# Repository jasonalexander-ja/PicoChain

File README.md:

# PicoChain

Pico(Daisy)Chain is a simple standard for creating daisy chains of connected devices, allowing I2C and power to be easily distributed out using ethernet patch cables. 

This is a repository containing documentation and reference hardware + software implementations. 

All hardware reference implementations are in KiCAD 8+ format with the PCB layout and Gerbers. 

### Contents: 

- [PicoChainReference](/PicoChainReference); A generic reference design breaking out the power and I2C to pin headers, this can be easily adapted to what ever purpose is desired. 
- [PicoChainZero](/PicoChainZero); A reference design using the Raspberry Pi Zero as a I2C controller, breaks out the Pi Zero's serial to a USB-C connector. 
- [PicoChainTerminator](/PicoChainTerminator); A reference design for a termination endpoint device, one of these needs to be present at the start and end of a chain. 

## Design Overview 

PicoChain uses differential I2C, 12 + 24 volts, all sent down a single RJ45 & twisted pair allowing communication and power for microcontrollers + motors to be supplied using commonly available ethernet patch cables. 

Generation of the differential I2C is handled by the [NXP PCA9615](https://www.nxp.com/docs/en/data-sheet/PCA9615.pdf) meaning that when SCL and SCA is hooked up to this chip, all the same I2C libraries and implementation automatically work with no further modifications. 

The 12 + 24 volts is supplied with the assumption that this will be regulated into the relevant required voltages by the connected devices, the reference implementations regulates a 5V for the microcontroller and a 5V for servo and similar small motors off of the 12V line, and a 12V line is regulated off of the 24V line intended for high power motors. 

Each PicoChain device has 2 RJ45 connectors to send and receive power and data, they don't have a particular direction are all the reference designs have the RJ45s passively connected, tapping off of power and I2C as needed, however, all PicoChain chains need terminators at either end. 

Generally, this is designed for running sequences across some connected devices, with the idea that only 1 large load (I.E. a motor) will be running at a time, reducing the current load going through the patch cables and chained devices. 

### Pinout 

| **RJ45 Pin** | **Function** |
|--------------|--------------|
| **1**        | GND          |
| **2**        | +24V         |
| **3**        | DSDAM        |
| **4**        | DSCLM        |
| **5**        | DSCLP        |
| **6**        | DSDAP        |
| **7**        | GND          |
| **8**        | +12V         |

Pins 3-6 (inclusive) are generated by the [PCA9615](https://www.nxp.com/docs/en/data-sheet/PCA9615.pdf) and are connected directly to ICs on each device.

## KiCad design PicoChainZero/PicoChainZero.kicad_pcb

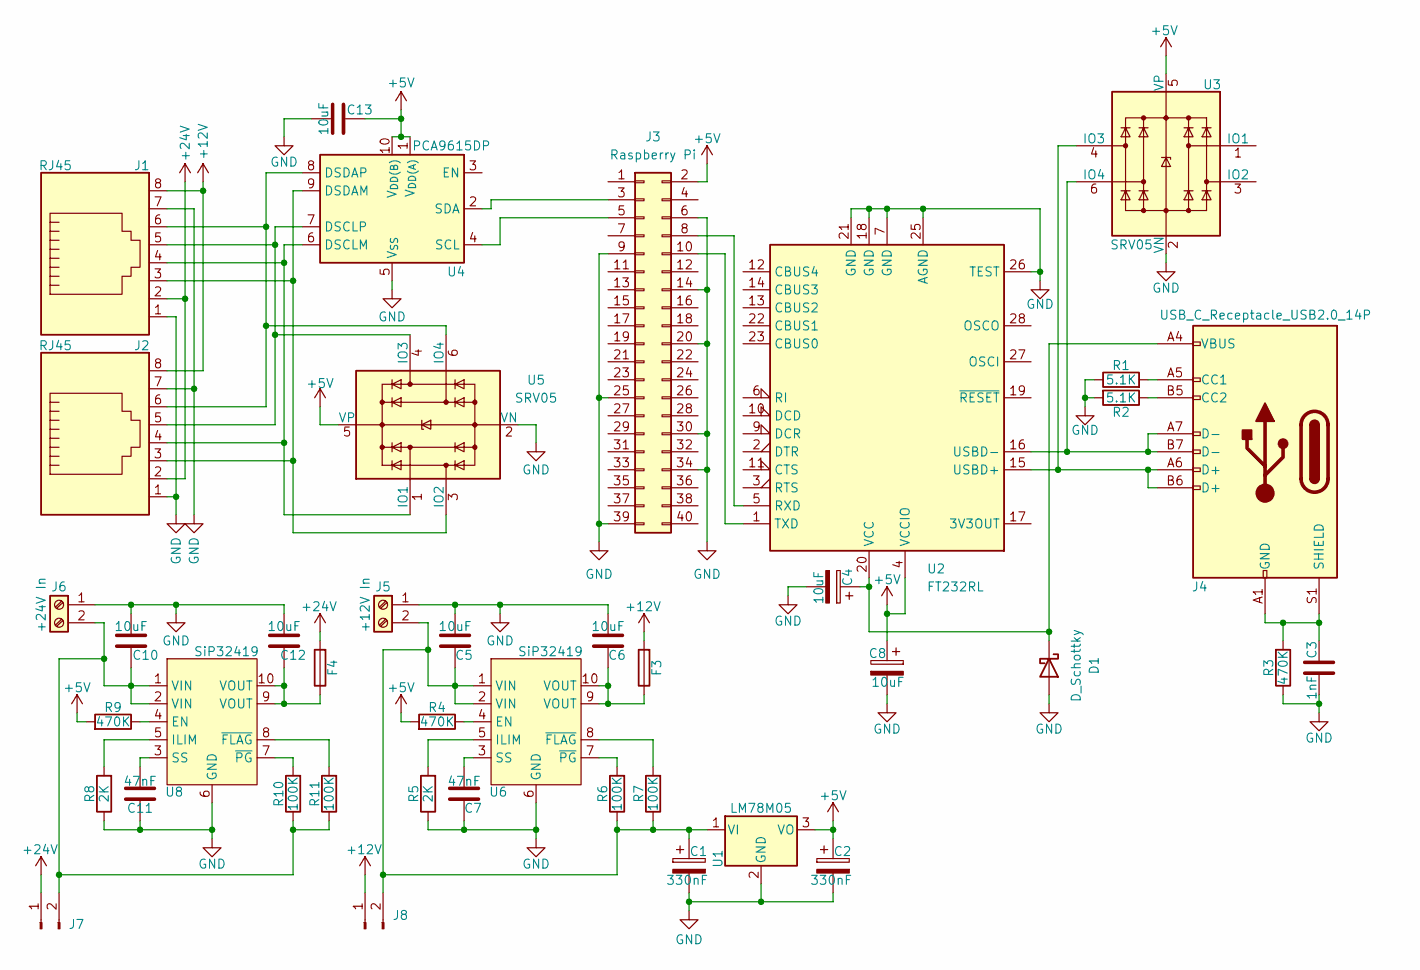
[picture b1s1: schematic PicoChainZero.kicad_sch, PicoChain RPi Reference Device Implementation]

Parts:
C1, C2: 330nF; CP_EIA-3216-18_Kemet-A
C3: 1nF; C_1206_3216Metric
C4, C8: 10uF; CP_EIA-3216-18_Kemet-A
C5, C6, C10, C12, C13: 10uF; C_0805_2012Metric
C7, C11: 47nF; C_0805_2012Metric
D1: D_Schottky; D_SMA
F3, F4: Fuse; Fuse_0805_2012Metric
J1, J2: RJ45; RJ45_Amphenol_54602-x08_Horizontal
J3: Raspberry Pi; PinHeader_2x20_P2.54mm_Vertical
J4: USB_C_Receptacle_USB2.0_14P; USB_C_Receptacle_GCT_USB4085
J5: +12V In; TerminalBlock_Phoenix_MKDS-1,5-2-5.08_1x02_P5.08mm_Horizont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
J6: +24V In; TerminalBlock_Phoenix_MKDS-1,5-2-5.08_1x02_P5.08mm_Horizont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
J7, J8: Conn_01x02_Pin; PinHeader_1x02_P2.54mm_Vertical
R1, R2: 5.1K; R_0805_2012Metric
R3, R4, R9: 470K; R_0805_2012Metric
R5, R8: 2K; R_0805_2012Metric
R6, R7, R10, R11: 100K; R_0805_2012Metric
U1: LM78M05; TO-252-2
U2: FT232RL; SSOP-28_5.3x10.2mm_P0.65mm
U3, U5: SRV05; SOT-23-6
U4: PCA9615DP; TSSOP-10_3x3mm_P0.5mm
U6, U8: SiP32419; DFN-10-1EP_3x3mm_P0.5mm_EP1.65x2.38mm

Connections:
+5V: C2.1, C8.1, C13.2, J3.2, R4.2, R9.2, U1.3 (VO), U2.4 (VCCIO), U3.5 (VP), U4.1 (V_{DD(A)}), U4.10 (V_{DD(B)}), U5.5 (VP)
+12V: F3.2, J1.8, J2.8, J8.1
+24V: F4.2, J1.2, J2.2, J7.1
GND: C1.2, C2.2, C3.2, C4.2, C5.1, C6.1, C7.2, C8.2, C10.1, C11.2, C12.1, C13.1, D1.2 (A), J1.1, J1.7, J2.1, J2.7, J3.6, J3.9, J3.14, J3.20, J3.25, J3.30, J3.34, J3.39, J5.1, J6.1, R1.1, R2.2, R3.1, R5.1, R8.1, U1.2 (GND), U2.7 (GND), U2.18 (GND), U2.21 (GND), U2.25 (AGND), U2.26 (TEST), U3.2 (VN), U4.5 (V_{SS}), U5.2 (VN), U6.6 (GND), U8.6 (GND)
unnamed: C6.2, F3.1, U6.9 (VOUT), U6.10 (VOUT)
unnamed: C12.2, F4.1, U8.9 (VOUT), U8.10 (VOUT)
unnamed: C4.1, D1.1 (K), J4.A4 (VBUS), J4.A9 (VBUS), J4.B4 (VBUS), J4.B9 (VBUS), U2.20 (VCC)
unnamed: J3.3, U4.2 (SDA)
unnamed: J3.5, U4.4 (SCL)
unnamed: J3.8, U2.5 (RXD)
unnamed: J3.10, U2.1 (TXD)
unnamed: J4.A5 (CC1), R1.2
unnamed: J4.B5 (CC2), R2.1
unnamed: C3.1, J4.A1 (GND), J4.A12 (GND), J4.B1 (GND), J4.B12 (GND), J4.S1 (SHIELD), R3.2
unnamed: C1.1, C5.2, J5.2, J8.2, R6.1, R7.1, U1.1 (VI), U6.1 (VIN), U6.2 (VIN)
unnamed: C10.2, J6.2, J7.2, R10.1, R11.1, U8.1 (VIN), U8.2 (VIN)
unnamed: J4.A6 (D+), J4.B6 (D+), U2.15 (USBD+), U3.4 (IO3)
unnamed: J4.A7 (D-), J4.B7 (D-), U2.16 (USBD-), U3.6 (IO4)
unnamed: J1.4, J2.4, U4.6 (DSCLM), U5.1 (IO1)
unnamed: J1.5, J2.5, U4.7 (DSCLP), U5.4 (IO3)
unnamed: J1.3, J2.3, U4.9 (DSDAM), U5.3 (IO2)
unnamed: J1.6, J2.6, U4.8 (DSDAP), U5.6 (IO4)
unnamed: R4.1, U6.4 (EN)
unnamed: R5.2, U6.5 (ILIM)
unnamed: C7.1, U6.3 (SS)
unnamed: R7.2, U6.8 (~FLAG)
unnamed: R6.2, U6.7 (~PG)
unnamed: R9.1, U8.4 (EN)
unnamed: R8.2, U8.5 (ILIM)
unnamed: C11.1, U8.3 (SS)
unnamed: R11.2, U8.8 (~FLAG)
unnamed: R10.2, U8.7 (~PG)

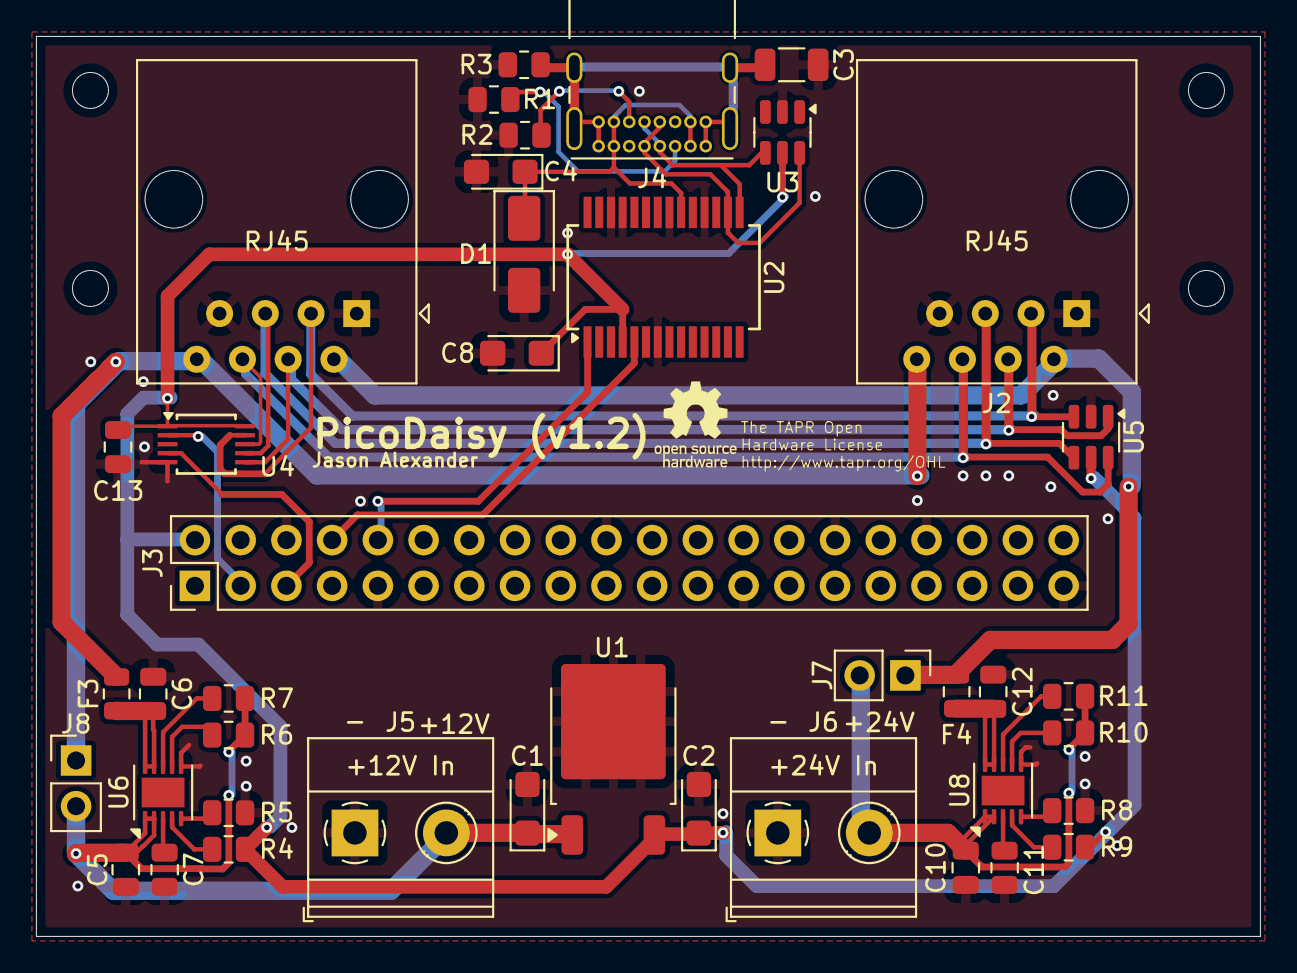
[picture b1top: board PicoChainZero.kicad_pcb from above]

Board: 4 copper layers, 68.0 x 50.0 mm, 41 parts (0 on the bottom side), 32 nets.

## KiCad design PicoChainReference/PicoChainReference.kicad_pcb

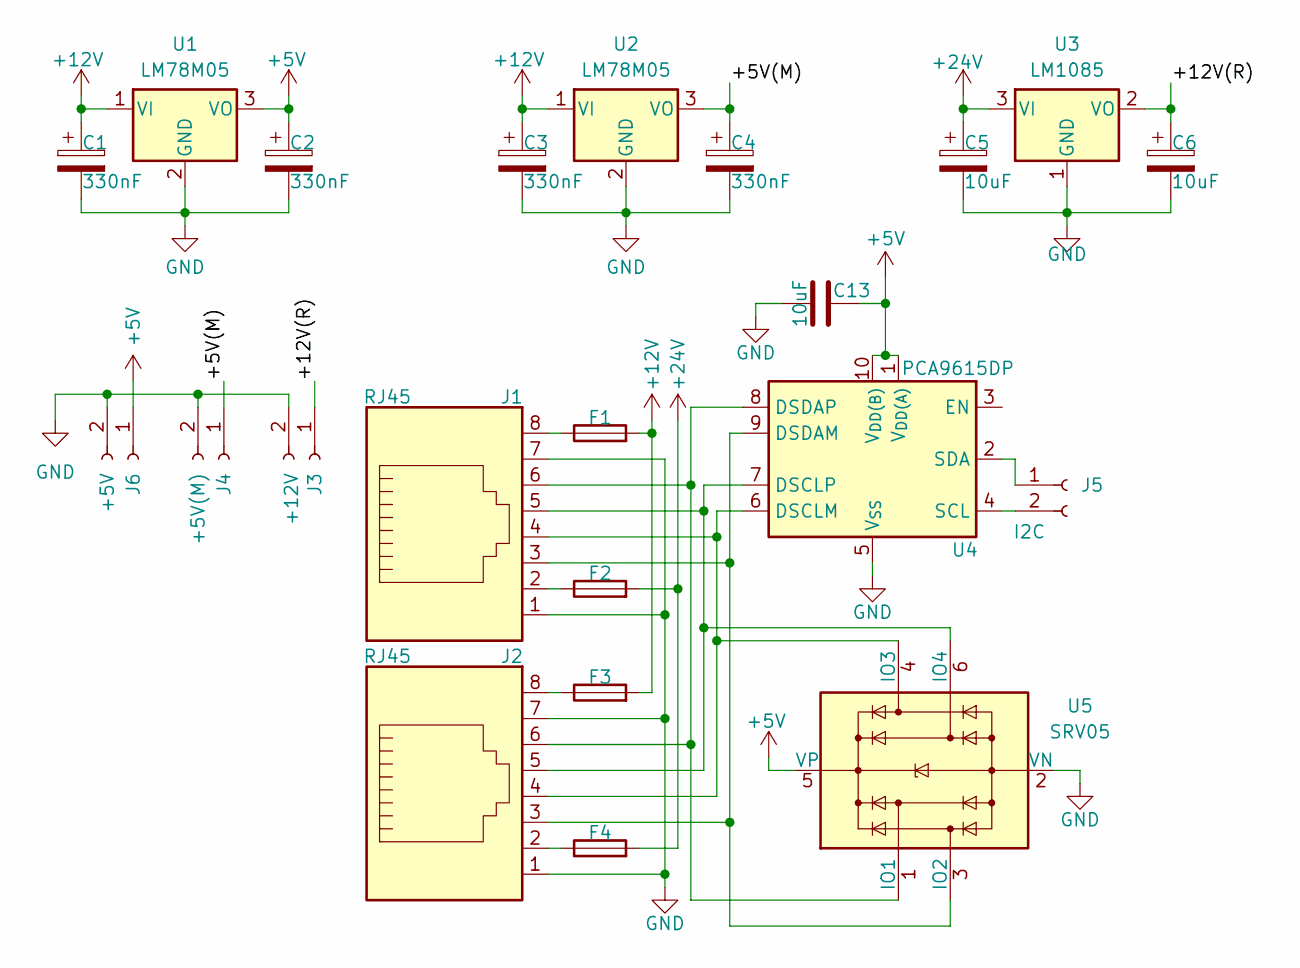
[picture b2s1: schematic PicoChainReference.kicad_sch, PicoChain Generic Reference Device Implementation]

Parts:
C1, C2, C3, C4: 330nF; CP_EIA-3216-18_Kemet-A
C5, C6: 10uF; CP_EIA-3528-21_Kemet-B
C13: 10uF; C_0805_2012Metric
F1, F2, F3, F4: Fuse; Fuse_0805_2012Metric
J1, J2: RJ45; RJ45_Amphenol_54602-x08_Horizontal
J3: +12V; PinHeader_1x02_P2.54mm_Vertical
J4: +5V(M); PinHeader_1x02_P2.54mm_Vertical
J5: I2C; PinHeader_1x02_P2.54mm_Vertical
J6: +5V; PinHeader_1x02_P2.54mm_Vertical
U1, U2: LM78M05; TO-252-2
U3: LM1085; TO254P1524X483-4N
U4: PCA9615DP; TSSOP-10_3x3mm_P0.5mm
U5: SRV05; SOT-23-6

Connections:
+5V: C2.1, C13.2, J6.1, U1.3 (VO), U4.1 (V_{DD(A)}), U4.10 (V_{DD(B)}), U5.5 (VP)
+12V: C1.1, C3.1, F1.2, F3.2, U1.1 (VI), U2.1 (VI)
+24V: C5.1, F2.2, F4.2, U3.3 (VI)
/+5V(M): C4.1, J4.1, U2.3 (VO)
/+12V(R): C6.1, J3.1, U3.2 (VO)
GND: C1.2, C2.2, C3.2, C4.2, C5.2, C6.2, C13.1, J1.1, J1.7, J2.1, J2.7, J3.2, J4.2, J6.2, U1.2 (GND), U2.2 (GND), U3.1 (GND), U4.5 (V_{SS}), U5.2 (VN)
unnamed: F1.1, J1.8
unnamed: F2.1, J1.2
unnamed: F3.1, J2.8
unnamed: F4.1, J2.2
unnamed: J5.1, U4.2 (SDA)
unnamed: J5.2, U4.4 (SCL)
unnamed: J1.4, J2.4, U4.6 (DSCLM), U5.4 (IO3)
unnamed: J1.5, J2.5, U4.7 (DSCLP), U5.6 (IO4)
unnamed: J1.3, J2.3, U4.9 (DSDAM), U5.3 (IO2)
unnamed: J1.6, J2.6, U4.8 (DSDAP), U5.1 (IO1)

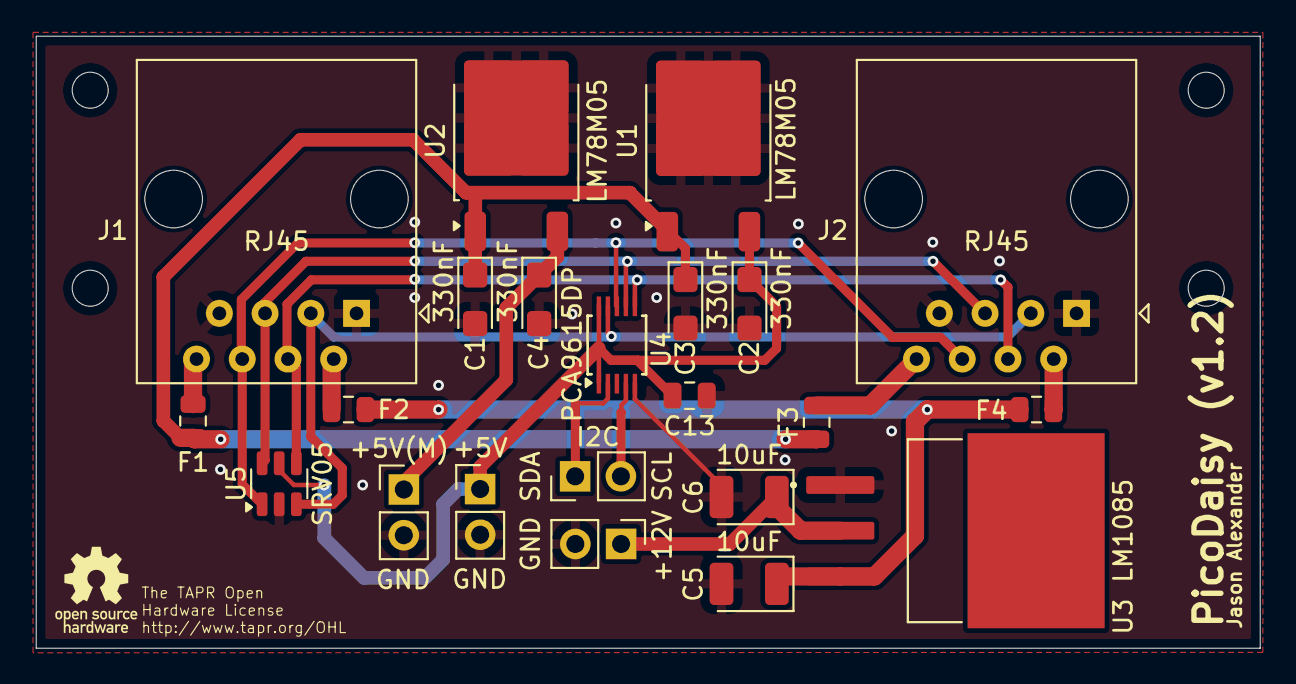
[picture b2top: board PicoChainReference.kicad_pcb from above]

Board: 4 copper layers, 68.0 x 34.0 mm, 22 parts (0 on the bottom side), 16 nets.

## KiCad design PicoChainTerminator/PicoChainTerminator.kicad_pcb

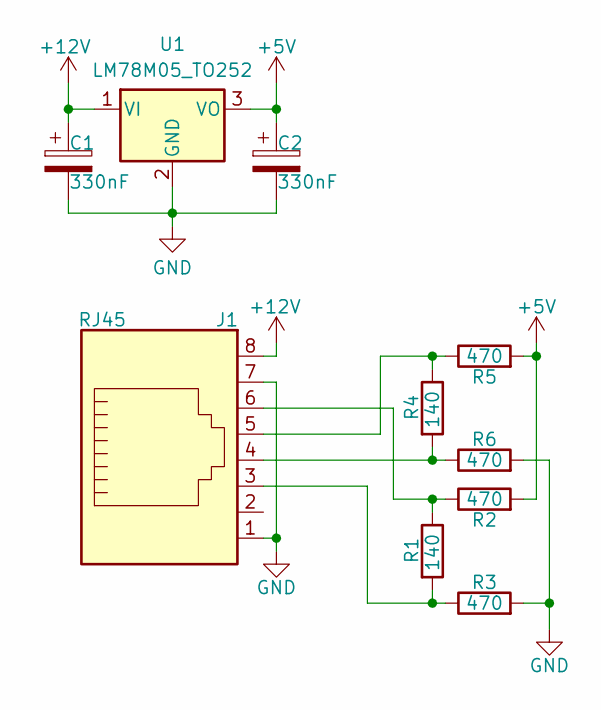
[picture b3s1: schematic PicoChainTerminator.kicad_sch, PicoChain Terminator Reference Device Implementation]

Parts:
C1, C2: 330nF; CP_EIA-3216-18_Kemet-A
J1: RJ45; RJ45_Amphenol_54602-x08_Horizontal
R1, R4: 140; R_0805_2012Metric
R2, R3, R5, R6: 470; R_0805_2012Metric
U1: LM78M05_TO252; TO-252-2

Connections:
+5V: C2.1, R2.2, R5.2, U1.3 (VO)
+12V: C1.1, J1.8, U1.1 (VI)
GND: C1.2, C2.2, J1.1, J1.7, R3.2, R6.2, U1.2 (GND)
unnamed: J1.3, R1.2, R3.1
unnamed: J1.4, R4.2, R6.1
unnamed: J1.5, R4.1, R5.1
unnamed: J1.6, R1.1, R2.1

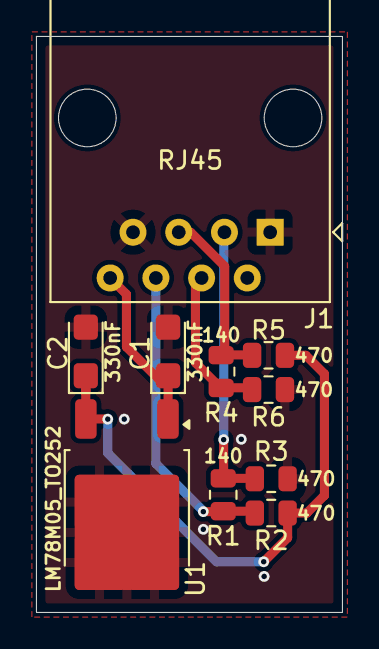
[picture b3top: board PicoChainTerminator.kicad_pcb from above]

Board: 4 copper layers, 17.0 x 32.0 mm, 10 parts (0 on the bottom side), 7 nets.

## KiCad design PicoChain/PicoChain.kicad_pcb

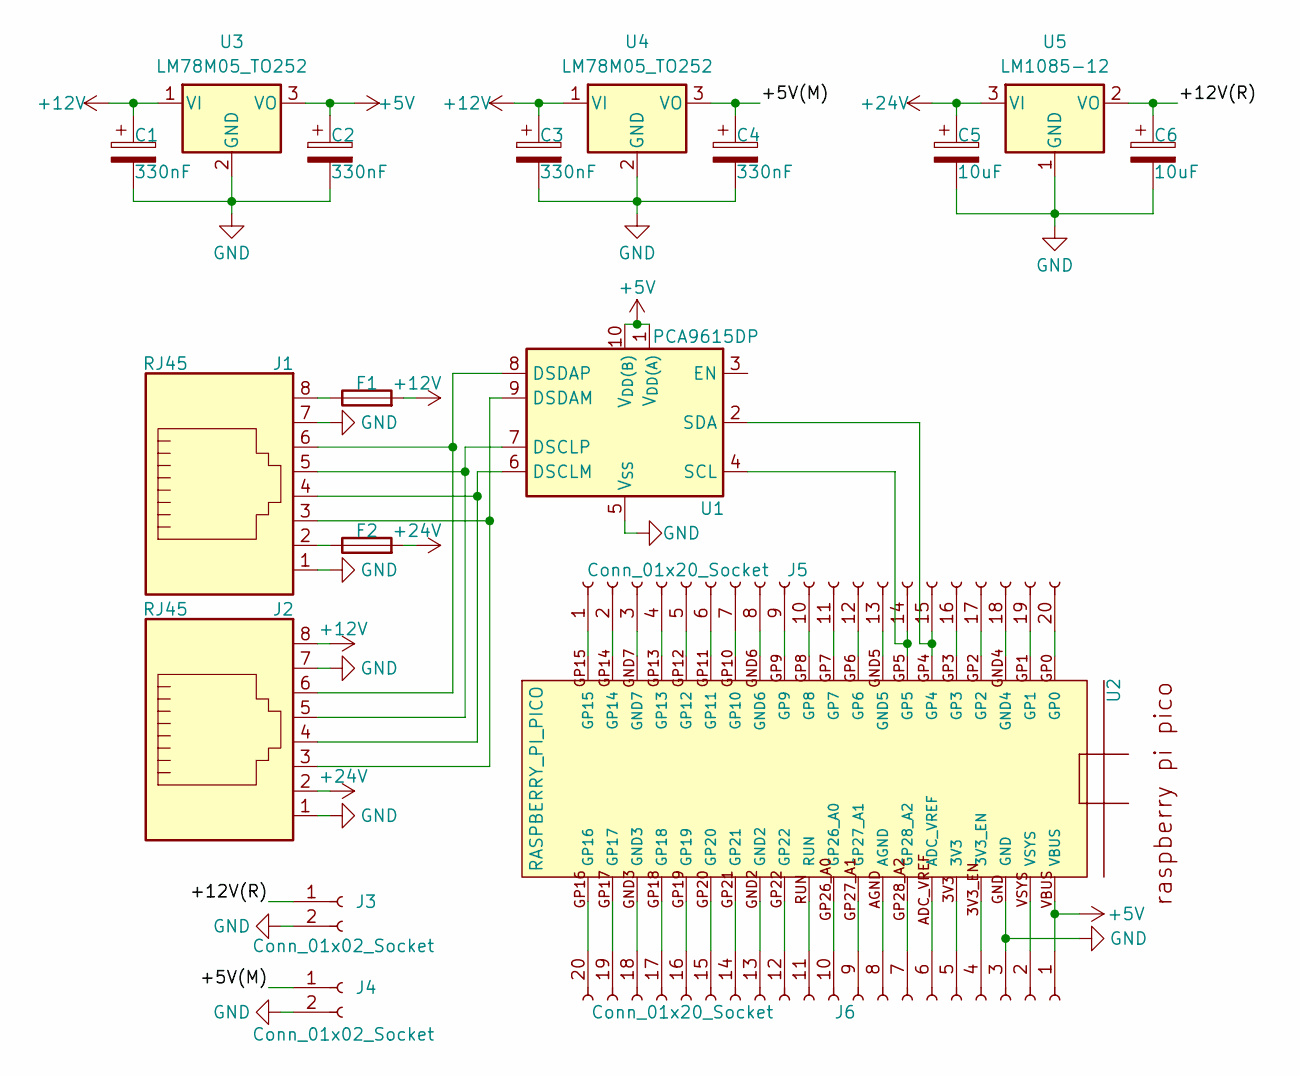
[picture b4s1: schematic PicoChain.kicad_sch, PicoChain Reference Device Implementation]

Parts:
C1, C2, C3, C4: 330nF; CP_EIA-3216-18_Kemet-A
C5, C6: 10uF; CP_EIA-3528-21_Kemet-B
F1, F2: Fuse; Fuse_0805_2012Metric
J1, J2: RJ45; RJ45_Amphenol_54602-x08_Horizontal
J3, J4: Conn_01x02_Socket; PinHeader_1x02_P2.54mm_Vertical
J5, J6: Conn_01x20_Socket; PinHeader_1x20_P2.54mm_Vertical
U1: PCA9615DP; TSSOP-10_3x3mm_P0.5mm
U2: RASPBERRY_PI_PICO
U3, U4: LM78M05_TO252; TO-252-2
U5: LM1085-12; TO254P1524X483-4N

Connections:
+5V: C2.1, J6.1, U1.1 (V_{DD(A)}), U1.10 (V_{DD(B)}), U2.VBUS, U3.3 (VO)
+12V: C1.1, C3.1, F1.2, J2.8, U3.1 (VI), U4.1 (VI)
+24V: C5.1, F2.2, J2.2, U5.3 (VI)
/+5V(M): C4.1, J4.1, U4.3 (VO)
/+12V(R): C6.1, J3.1, U5.2 (VO)
GND: C1.2, C2.2, C3.2, C4.2, C5.2, C6.2, J1.1, J1.7, J2.1, J2.7, J3.2, J4.2, J6.3, U1.5 (V_{SS}), U2.GND, U3.2 (GND), U4.2 (GND), U5.1 (GND)
unnamed: F1.1, J1.8
unnamed: F2.1, J1.2
unnamed: J5.1, U2.GP15
unnamed: J5.2, U2.GP14
unnamed: J5.3, U2.GND7
unnamed: J5.4, U2.GP13
unnamed: J5.5, U2.GP12
unnamed: J5.6, U2.GP11
unnamed: J5.7, U2.GP10
unnamed: J5.8, U2.GND6
unnamed: J5.9, U2.GP9
unnamed: J5.10, U2.GP8
unnamed: J5.11, U2.GP7
unnamed: J5.12, U2.GP6
unnamed: J5.13, U2.GND5
unnamed: J5.14, U1.4 (SCL), U2.GP5
unnamed: J5.15, U1.2 (SDA), U2.GP4
unnamed: J5.16, U2.GP3
unnamed: J5.17, U2.GP2
unnamed: J5.18, U2.GND4
unnamed: J5.19, U2.GP1
unnamed: J5.20, U2.GP0
unnamed: J6.2, U2.VSYS
unnamed: J6.4, U2.3V3_EN
unnamed: J6.5, U2.3V3
unnamed: J6.6, U2.ADC_VREF
unnamed: J6.7, U2.GP28_A2
unnamed: J6.8, U2.AGND
unnamed: J6.9, U2.GP27_A1
unnamed: J6.10, U2.GP26_A0
unnamed: J6.11, U2.RUN
unnamed: J6.12, U2.GP22
unnamed: J6.13, U2.GND2
unnamed: J6.14, U2.GP21
unnamed: J6.15, U2.GP20
unnamed: J6.16, U2.GP19
unnamed: J6.17, U2.GP18
unnamed: J6.18, U2.GND3
unnamed: J6.19, U2.GP17
unnamed: J6.20, U2.GP16
unnamed: J1.4, J2.4, U1.6 (DSCLM)
unnamed: J1.5, J2.5, U1.7 (DSCLP)
unnamed: J1.3, J2.3, U1.9 (DSDAM)
unnamed: J1.6, J2.6, U1.8 (DSDAP)

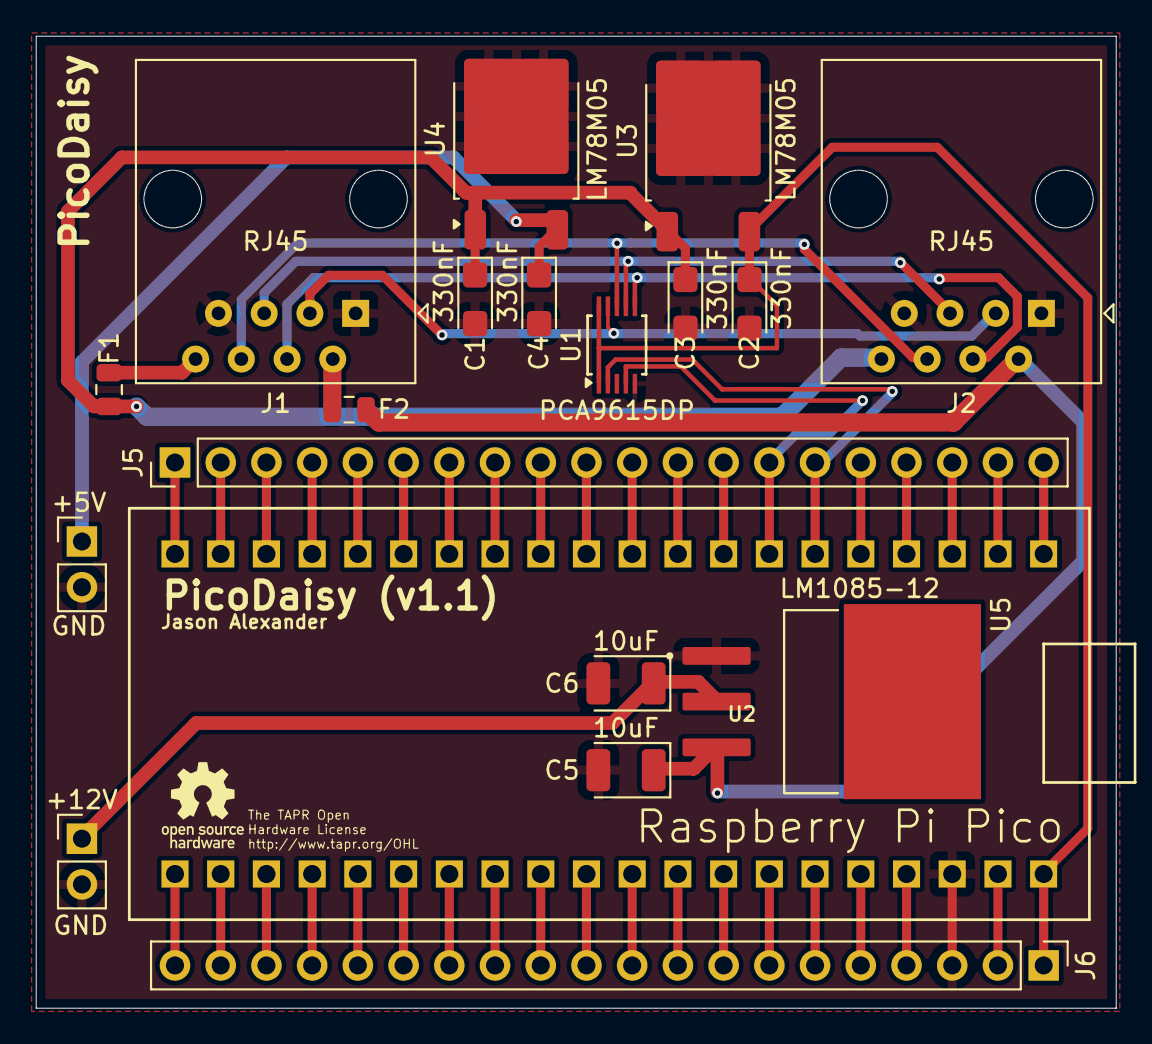
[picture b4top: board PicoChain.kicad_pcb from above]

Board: 4 copper layers, 60.0 x 54.0 mm, 19 parts (0 on the bottom side), 50 nets.

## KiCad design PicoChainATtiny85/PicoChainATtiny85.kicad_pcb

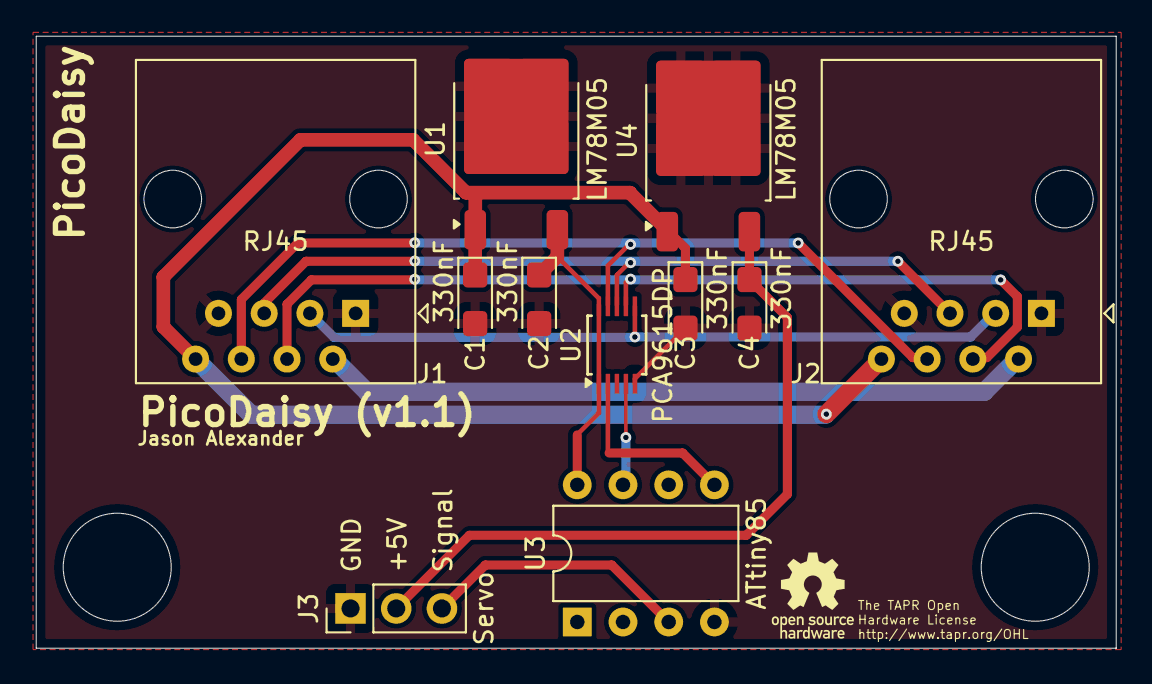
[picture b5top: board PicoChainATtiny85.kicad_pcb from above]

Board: 2 copper layers, 60.0 x 34.0 mm, 11 parts (0 on the bottom side), 12 nets.

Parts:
C1, C2, C3, C4: 330nF; CP_EIA-3216-18_Kemet-A
J1, J2: RJ45; RJ45_Amphenol_54602-x08_Horizontal
J3: Servo; PinHeader_1x03_P2.54mm_Vertical
U1, U4: LM78M05; TO-252-2
U2: PCA9615DP; TSSOP-10_3x3mm_P0.5mm
U3: ATtiny85; DIP-8_W7.62mm

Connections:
+5V: C2.1, U1.3 (VO), U2.1 (V_{DD(A)}), U2.10 (V_{DD(B)}), U3.8 (VCC)
+12V: C1.1, C3.1, J1.8, J2.8, U1.1 (VI), U4.1 (VI)
+24V: J1.2, J2.2
/+5V(M): C4.1, J3.2, U4.3 (VO)
GND: C1.2, C2.2, C3.2, C4.2, J1.1, J1.7, J2.1, J2.7, J3.1, U1.2 (GND), U2.5 (V_{SS}), U3.4 (GND), U4.2 (GND)
unnamed: J3.3, U3.3 (XTAL2/PB4)
unnamed: J1.3, J2.3, U2.6 (DSCLM)
unnamed: J1.4, J2.4, U2.7 (DSCLP)
unnamed: J1.6, J2.6, U2.9 (DSDAM)
unnamed: J1.5, J2.5, U2.8 (DSDAP)
unnamed: U2.4 (SCL), U3.7 (PB2)
unnamed: U2.2 (SDA), U3.5 (AREF/PB0)

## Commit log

2024-08-12 Initial commit.
2024-08-14 Updated to version 1.1
2024-08-17 Added reference design
2024-08-22 Finished off more reference designs and added readme
2024-08-22 Updated gitignore.
2024-08-22 Added licences and PDF schematics
2024-08-22 Added open source hardware logo to PCBs
2024-08-22 Added terminator reference design
2024-08-22 Regenerated gerbers
2024-08-22 Updated PDF schematic.
2024-08-23 Made pass through power rails larger.
2025-02-14 Updated PicoChainZero base board.
2025-02-14 Added PicoChainZero baseboard schematic PDF
2025-02-15 Updated PicoChainZero PCB layout and generated Gerbers.
2025-02-15 Updated pdf schematic for PicoChainZero.
2025-04-20 Updated to 1.2
2025-04-21 Added more fuses to reference implementation
2025-07-12 Updated example reference gerber files to remove extra inner PCB layers
2025-07-20 Added decoupling capacitors to dI2C drivers (doh)
2025-07-21 Adjustments to PicoChainZero
2025-07-21 Adjusted schematics
2025-07-23 Finial changes before ordering first boards.
2025-08-11 Added BOMs

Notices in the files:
PicoChain/PicoChain.kicad_pcb:
Licence: The TAPR Open Hardware License
